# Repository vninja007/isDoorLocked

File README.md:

# isDoorLocked
Title says it all. No need to go down the stairs on repeat.

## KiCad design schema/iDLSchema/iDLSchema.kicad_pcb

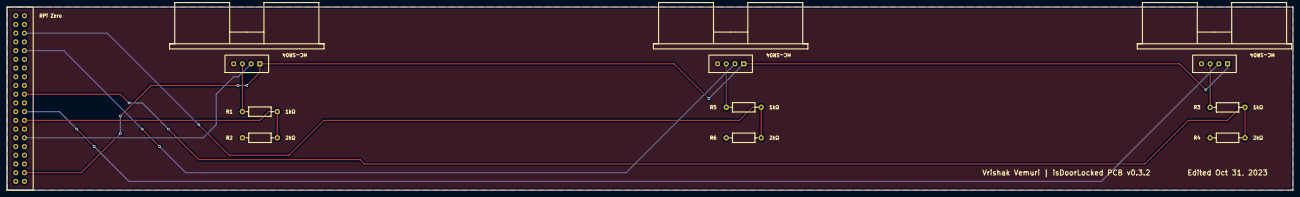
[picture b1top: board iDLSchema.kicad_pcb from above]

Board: 2 copper layers, 374.6 x 53.3 mm, 10 parts (0 on the bottom side), 11 nets.

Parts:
R1, R3, R5: 1kΩ; R_Axial_DIN0207_L6.3mm_D2.5mm_P10.16mm_Horizontal
R2, R4, R6: 2kΩ; R_Axial_DIN0207_L6.3mm_D2.5mm_P10.16mm_Horizontal
RPi Zero: Raspberry_Pi_Zero_W; Raspberry Pi Zero
U1, U2, U3: HC-SR04

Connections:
GND: R2.1, R4.2, R6.2, RPi Zero.14 (GND), U1.4 (GND), U2.4 (GND), U3.4 (GND)
unnamed: RPi Zero.12 (GPIO18), U1.2 (TRIG)
unnamed: R1.2, R2.2, RPi Zero.16 (GPIO23)
unnamed: RPi Zero.18 (GPIO24), U2.2 (TRIG)
unnamed: R3.2, R4.1, RPi Zero.22 (GPIO25)
unnamed: RPi Zero.32 (GPIO12), U3.2 (TRIG)
unnamed: R5.2, R6.1, RPi Zero.36 (GPIO16)
unnamed: R1.1, U1.3 (ECHO)
unnamed: R3.1, U2.3 (ECHO)
unnamed: R5.1, U3.3 (ECHO)
micro-USB: RPi Zero.4 (5V), U1.1 (VCC), U2.1 (VCC), U3.1 (VCC)

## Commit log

2023-09-17 projectdoc
2023-09-18 pretty good model imo
2023-09-18 modelkindabad
2023-10-02 finally able to know what is a circle.
2023-10-02 decent canny edge
2023-10-17 some line reg testing
2023-10-22 Going with template transforms now.
2023-10-22 template identification is very good!!!!
2023-10-29 most recent run
2023-10-29 stable comparision and detection
2023-10-29 new similarity scores
2023-10-29 template matching done
2023-10-29 schema done
2023-10-30 schema v0.2
2023-10-30 finished footprints
2023-10-31 putting my name on it lol
2023-10-31 new labelling
2023-10-31 layer rev, need to put a ne t
2023-10-31 new gerbers
2023-11-05 dem gerbers
2023-11-06 fullcode for actual testing
2023-11-06 upload mimics
2023-11-06 AIO upload working
